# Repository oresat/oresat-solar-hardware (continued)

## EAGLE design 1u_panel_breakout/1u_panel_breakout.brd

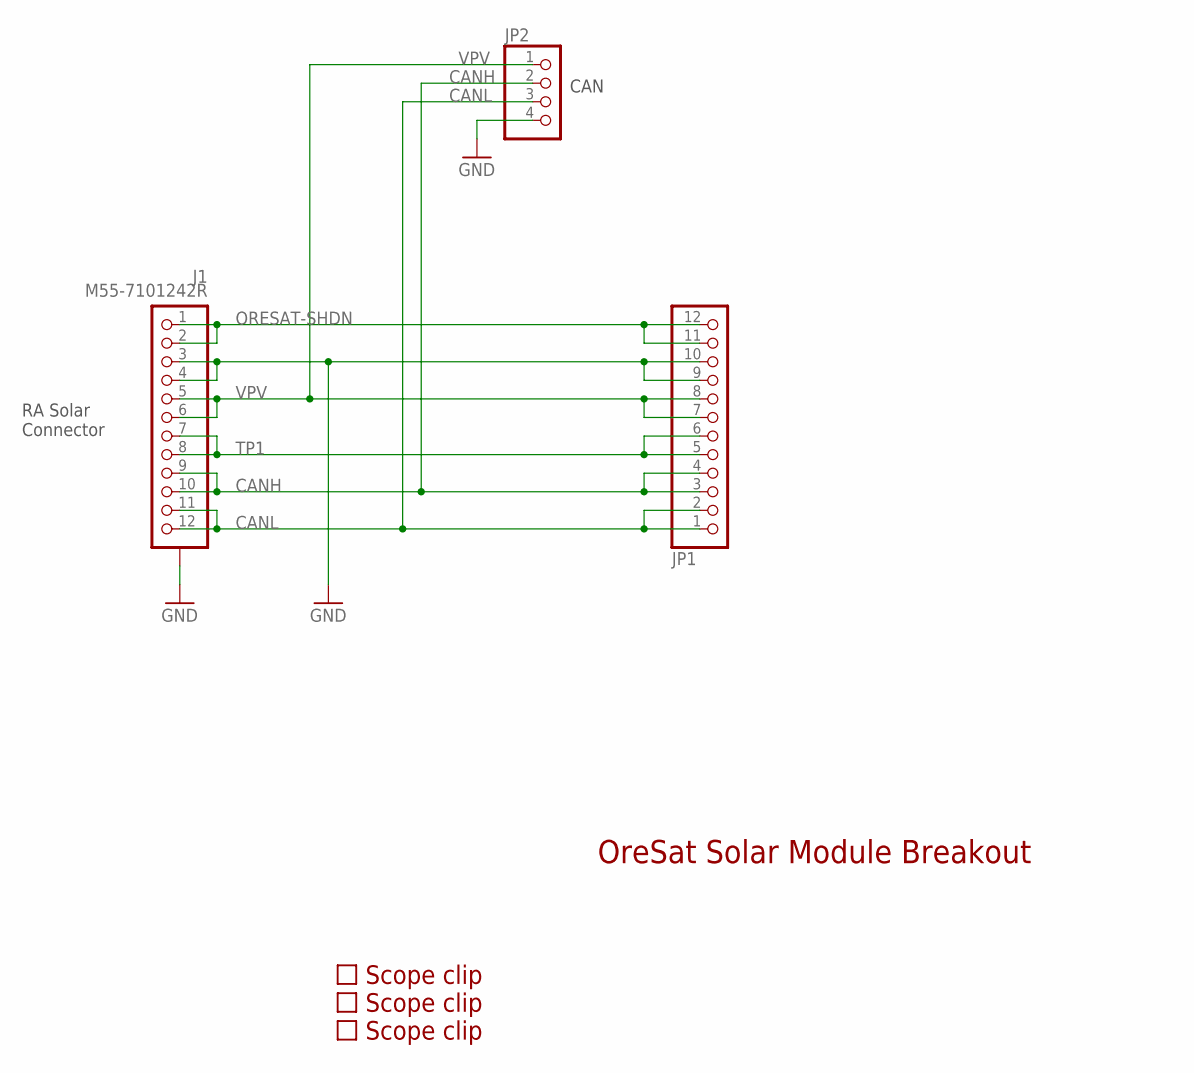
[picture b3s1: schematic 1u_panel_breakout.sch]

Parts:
J1: M55-7101242R
JP1: PINHD-1X12; 1X12
JP2: PINHD-1X4; 1X04
U$1, U$2, U$3: SCOPE_CLIP

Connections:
CANH: J1.9, J1.10, JP1.3, JP1.4, JP2.2
CANL: J1.11, J1.12, JP1.1, JP1.2, JP2.3
GND: J1.3, J1.4, J1.P$1 (SHIELD), J1.P$2 (SHIELD), J1.P$3 (SHIELD), J1.P$4 (SHIELD), JP1.9, JP1.10, JP2.4
ORESAT-SHDN: J1.1, J1.2, JP1.11, JP1.12
TP1: J1.7, J1.8, JP1.5, JP1.6
VPV: J1.5, J1.6, JP1.7, JP1.8, JP2.1

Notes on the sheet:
OreSat Solar Module Breakout
RA Solar Connector
CAN

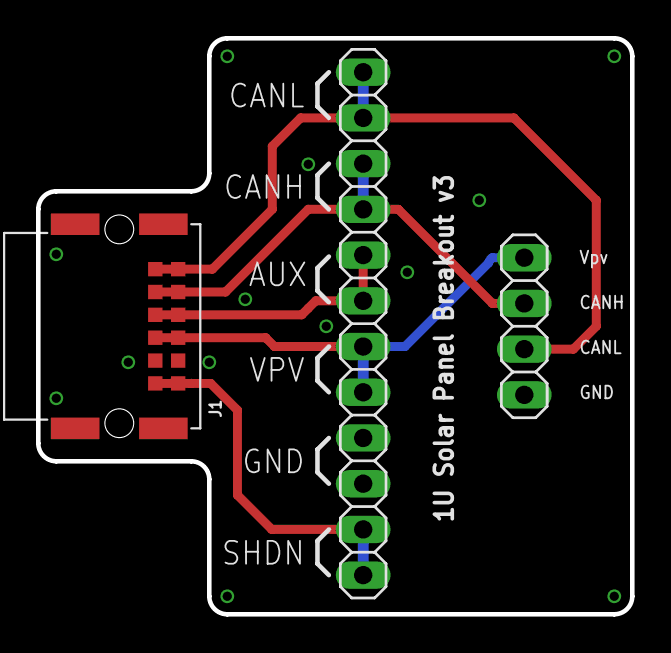
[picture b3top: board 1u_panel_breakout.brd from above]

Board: 2 copper layers, 33.0 x 32.0 mm, 6 parts (0 on the bottom side), 6 nets.

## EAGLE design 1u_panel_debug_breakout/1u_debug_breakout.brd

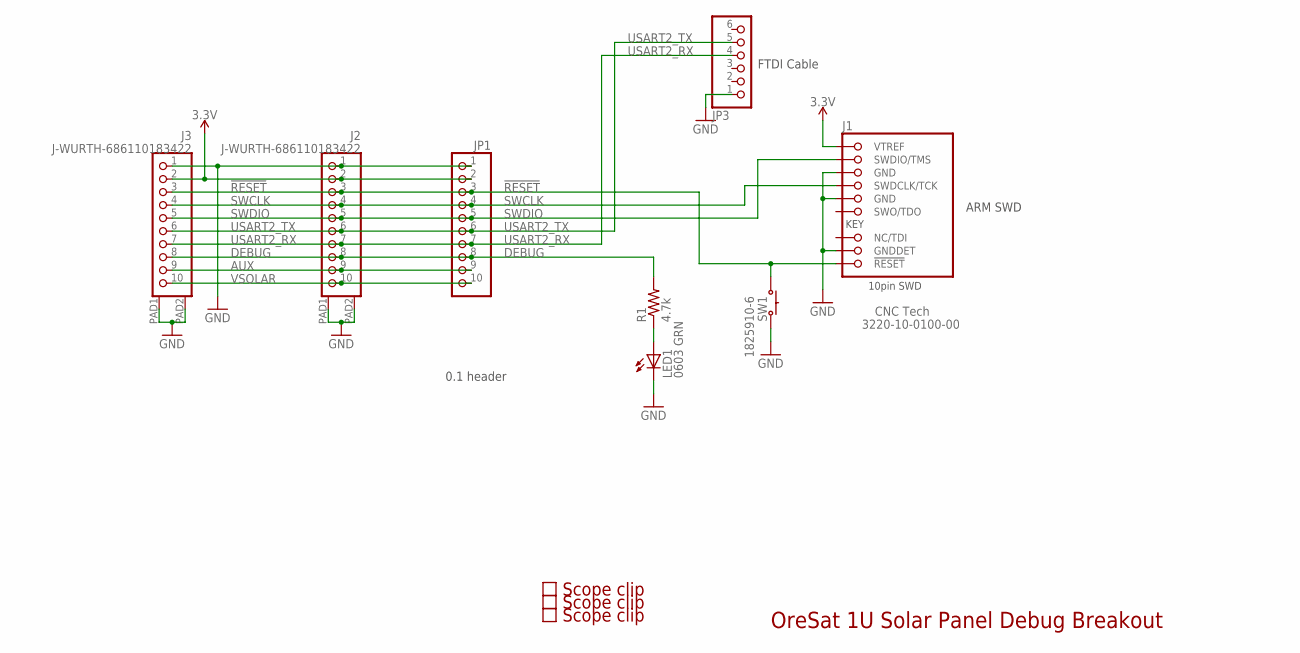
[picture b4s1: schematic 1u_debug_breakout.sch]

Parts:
J1: 1.27MM-SWD-CONNECTOR; 1.27MM_2X5; MPN 3220-10-0100-00
J2, J3: J-WURTH-686110183422
JP1: PINHD-1X10; 1X10
JP3: PINHD-1X6; 1X06
LED1: 0603 GRN; CHIPLED_0603
R1: 4.7k; R0603
SW1: 1825910-6; SWITCH_FSM4JAH
U$1, U$2, U$3: SCOPE_CLIP

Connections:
3.3V: J1.VTREF, J2.2, J3.2, JP1.2
!RESET: J1.!RESET, J2.3, J3.3, JP1.3, SW1.1, SW1.2 (1)
AUX: J2.9, J3.9, JP1.9
DEBUG: J2.8, J3.8, JP1.8, R1.2
GND: J1.GND, J1.GND@2 (GND), J1.GNDDET, J2.1, J2.PAD1, J2.PAD2, J3.1, J3.PAD1, J3.PAD2, JP1.1, JP3.1, LED1.C, SW1.3 (2), SW1.4 (2)
unnamed: LED1.A, R1.1
SWCLK: J1.SWDCLK (SWDCLK/TCK), J2.4, J3.4, JP1.4
SWDIO: J1.SWDIO (SWDIO/TMS), J2.5, J3.5, JP1.5
USART2_RX: J2.7, J3.7, JP1.7, JP3.4
USART2_TX: J2.6, J3.6, JP1.6, JP3.5
VSOLAR: J2.10, J3.10, JP1.10

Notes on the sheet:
OreSat 1U Solar Panel Debug Breakout
0.1 header
FTDI Cable
ARM SWD

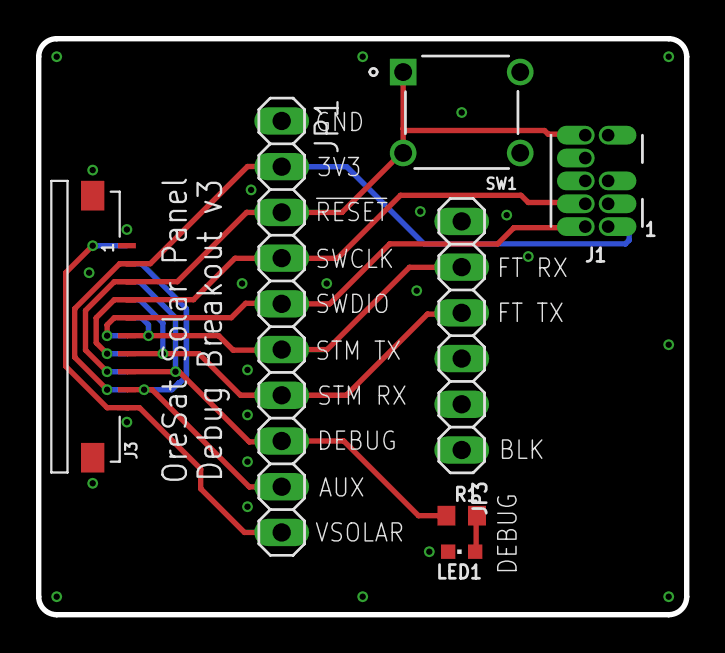
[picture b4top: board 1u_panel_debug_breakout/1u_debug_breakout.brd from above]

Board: 2 copper layers, 36.0 x 32.0 mm, 11 parts (1 on the bottom side), 11 nets.

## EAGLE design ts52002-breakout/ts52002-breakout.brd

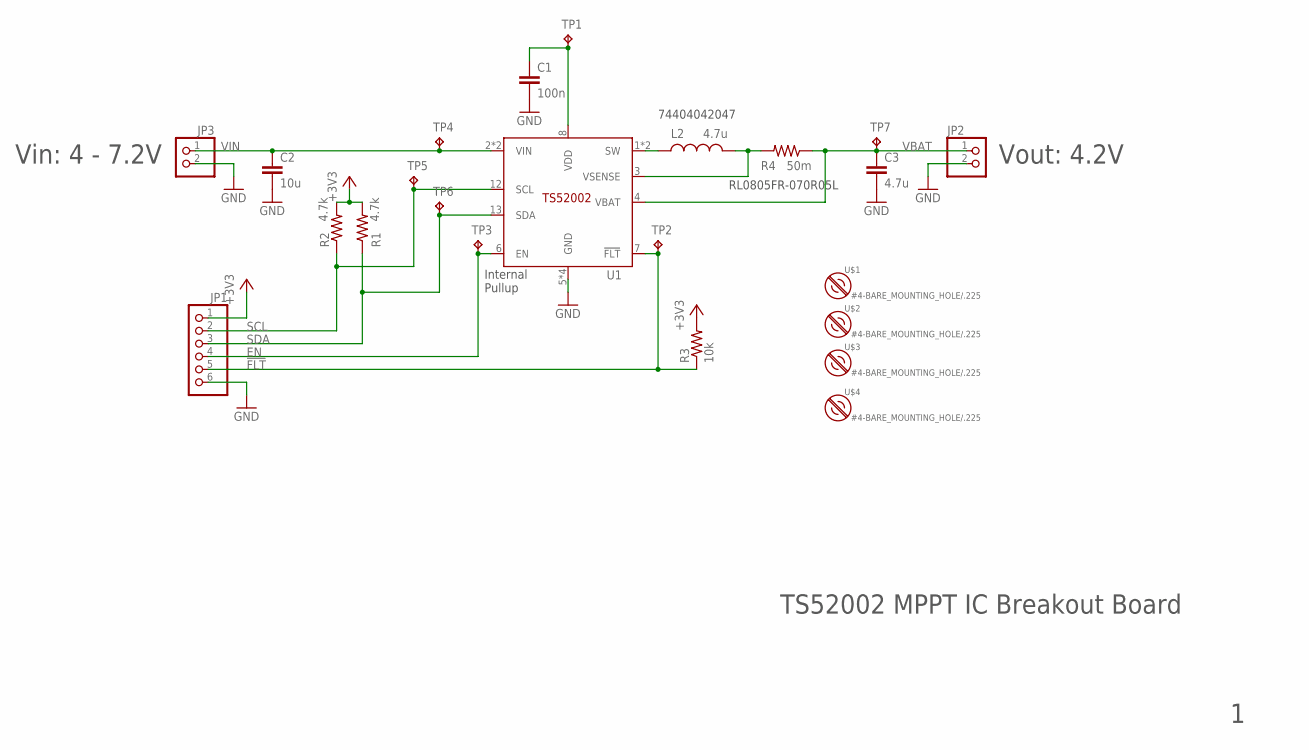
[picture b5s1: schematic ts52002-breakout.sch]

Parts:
C1: 100n; .0603-B-NOSILK
C2: 10u; .0805-B-NOSILK
C3: 4.7u; .0805-B-NOSILK
JP1: PINHD-1X6; 1X06
JP2, JP3: PINHD-1X2; 1X02
L2: 4.7u; WURTH-4518
R1, R2: 4.7k; .0603-B-NOSILK
R3: 10k; .0603-B-NOSILK
R4: 50m; .0805-B-NOSILK
TP1, TP2, TP3, TP4, TP5, TP6, TP7: TPPAD1-13; P1-13
U1: TS52002; QFN-32-WITH-CENTER-PAD
U$1, U$2, U$3, U$4: #4-BARE_MOUNTING_HOLE/.225; #4/.225-BARE+HEAD_OR_SMALL_NUT

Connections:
!FLT: JP1.5, R3.1, TP2.TP, U1.7 (!FLT)
+3V3: JP1.1, R1.2, R2.2, R3.2
EN: JP1.4, TP3.TP, U1.6 (EN)
GND: C1.2, C2.2, C3.2, JP1.6, JP2.2, JP3.2, U1.5 (GND), U1.15 (GND), U1.16 (GND), U1.PAD (GND)
SCL: JP1.2, R2.1, TP5.TP, U1.12 (SCL)
SDA: JP1.3, R1.1, TP6.TP, U1.13 (SDA)
SW: L2.P$1 (1), U1.1 (SW), U1.14 (SW)
VBAT: C3.1, JP2.1, R4.1, TP7.TP, U1.4 (VBAT)
VDD: C1.1, TP1.TP, U1.8 (VDD)
VIN: C2.1, JP3.1, TP4.TP, U1.2 (VIN), U1.11 (VIN)
VSENSE: L2.P$2 (2), R4.2, U1.3 (VSENSE)

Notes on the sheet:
74404042047
RL0805FR-070R05L
TS52002 MPPT IC Breakout Board
Vin: 4 - 7.2V
Vout: 4.2V
Internal Pullup

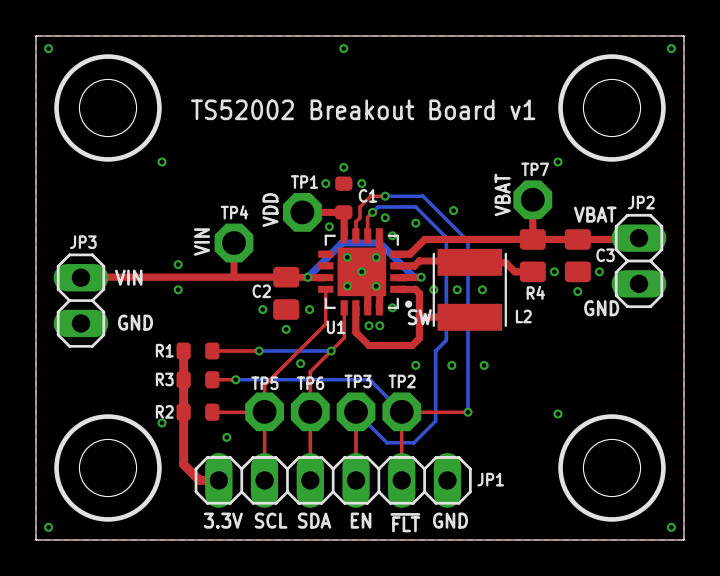
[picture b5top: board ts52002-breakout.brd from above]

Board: 2 copper layers, 36.0 x 28.0 mm, 23 parts (0 on the bottom side), 11 nets.

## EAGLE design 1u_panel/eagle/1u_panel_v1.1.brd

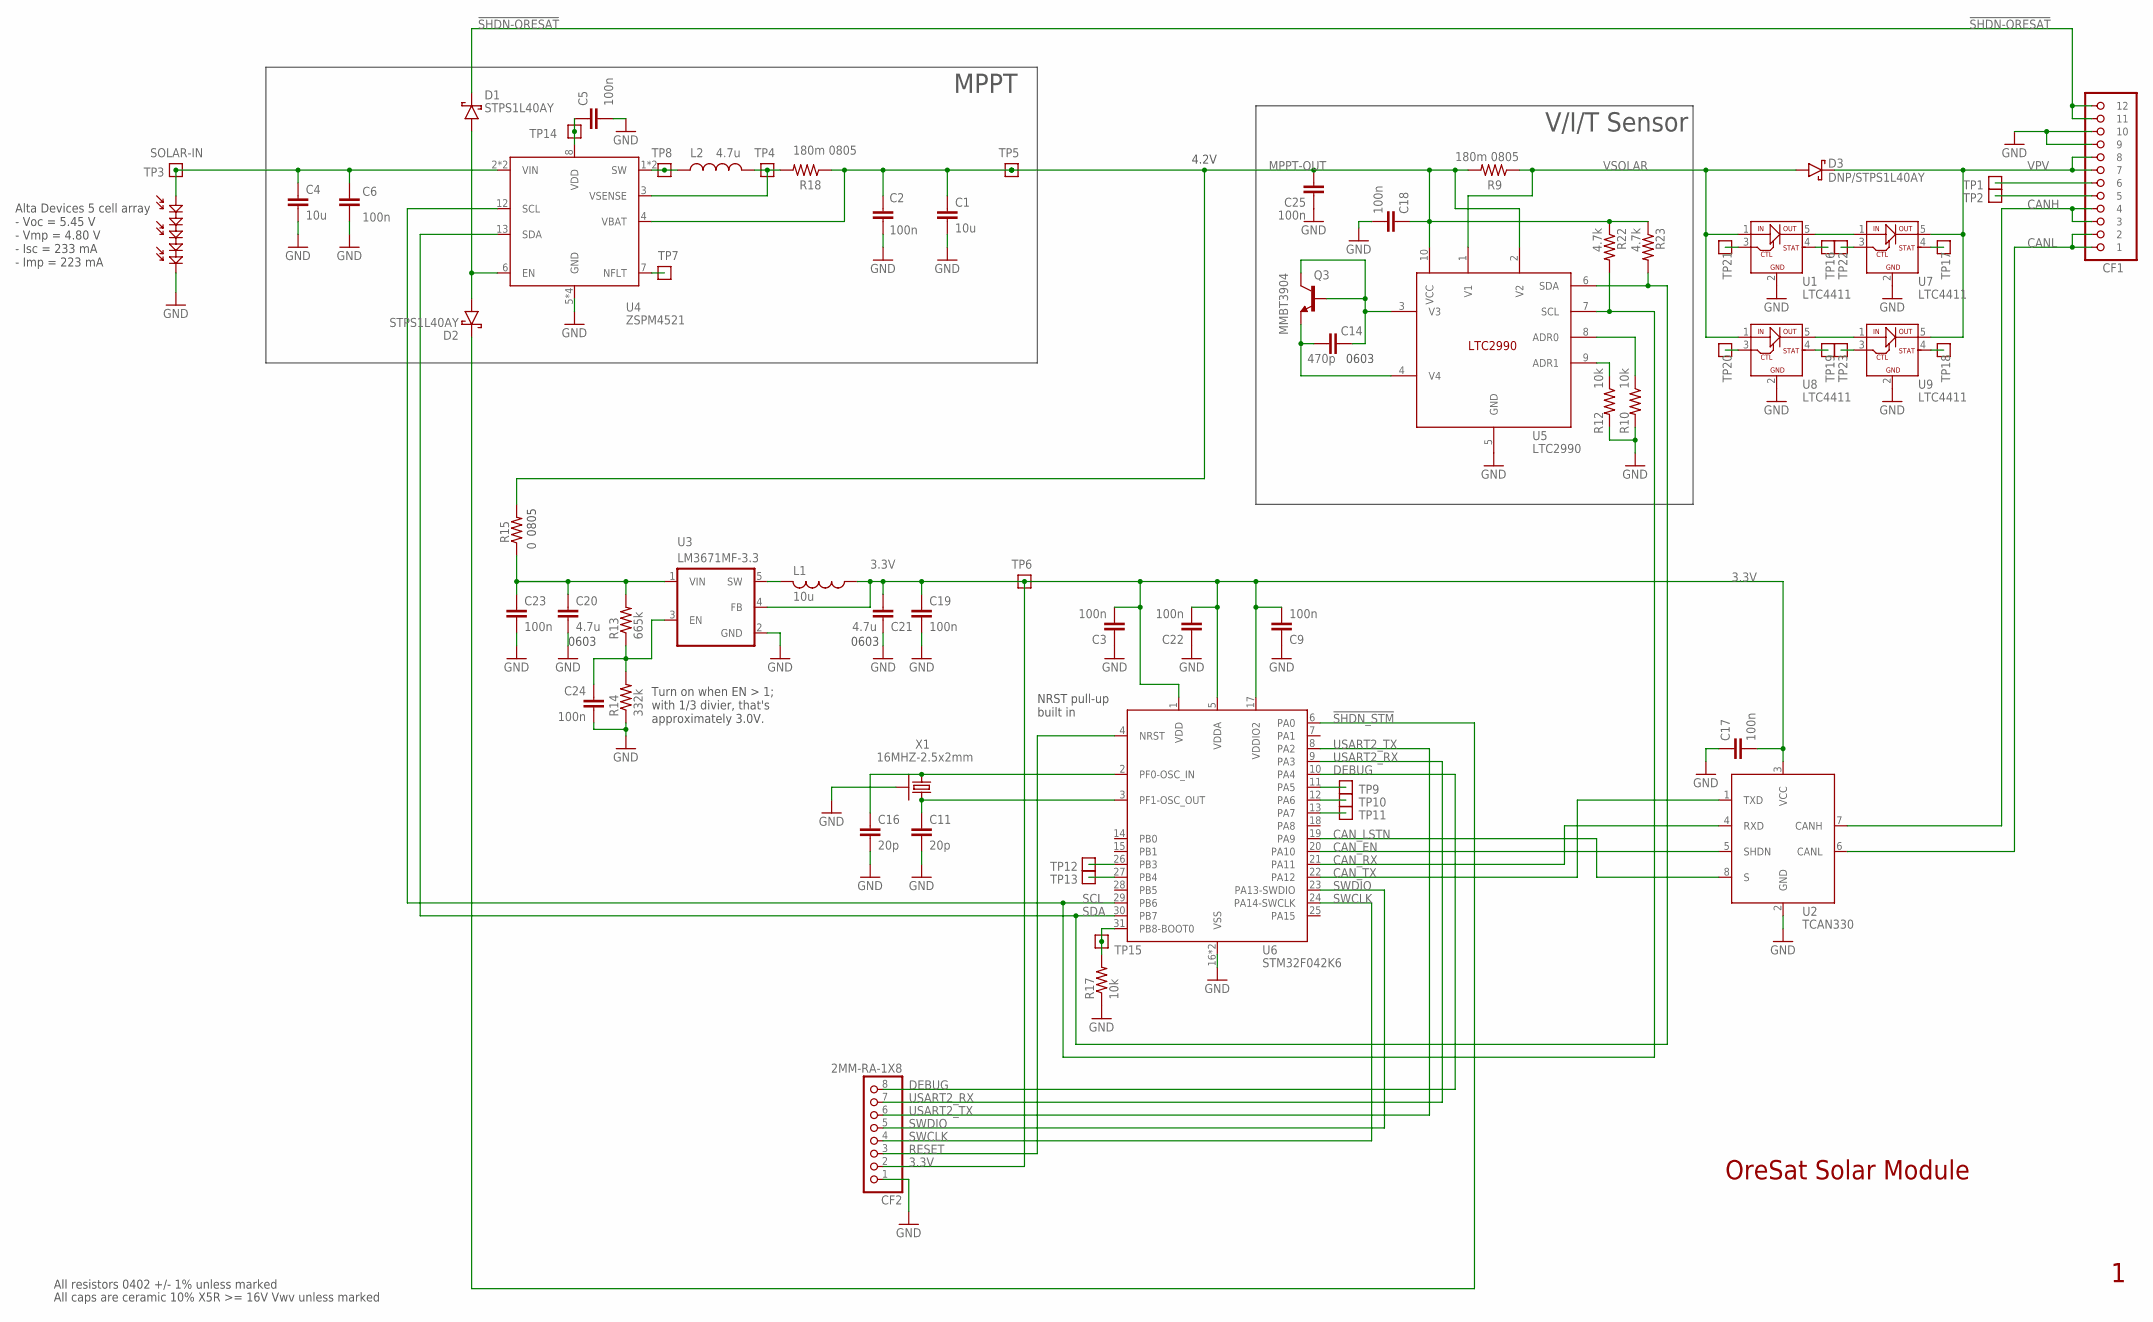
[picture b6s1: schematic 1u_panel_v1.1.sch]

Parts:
C1, C4: 10u; 1206-B; MPN GRM31CR71A226KE15L
C2, C3, C5, C6, C9, C17, C18, C19, C22, C23, C24, C25: 100n; .0402-B-NOSILK; MPN CL05B104KO5NNNC
C11, C16: 20p; .0402-B-NOSILK; MPN CL05C200JB51PNC
C14: 470p; .0603-B-NOSILK; MPN CL10A226MP8NUNE
C20, C21: 4.7u; C0603; MPN CL05B104KO5NNNC
CF1: 15220122401000; CON-1.27-F-HARTING-1522012X601XXX; MPN 15220122401000
CF2: 2MM-RA-1X8; CF-2MM-RA-1X8-PRECIDIP-831; MPN 831-87-050-40-001101
D1, D2: STPS1L40AY; DO214AC; MPN STPS1L40AY
D3: DNP/STPS1L40AY; DO214AC; MPN STPS1L40AY
L1: 10u; L2012C; MPN CB2012T100KR
L2: 4.7u; VISHAY-DALE-IFSR-1515AHER; MPN IFSC1515AHER220M01
PV1: ALTA-5-CELL-ARRAYALTA-FIVE-CELL-SLOT; ALTA-FIVE-CELL-THROUGH-SLOT
Q3: MMBT3904; SOT23HOLE; MPN MMBT3904
R9, R18: 180m 0805; .0805-B-NOSILK; MPN RCWE0805R180FKEA
R10, R12: 10k; .0402-B-NOSILK; MPN MCR01MZPF1002
R13: 665k; .0402-B-NOSILK; MPN RC1005F6653CS
R14: 332k; .0402-B-NOSILK; MPN RC1005F3323CS
R15: 0; .0805-B-NOSILK; MPN MCR10EZPJ000
R17: 10k; .0402-B-NOSILK; MPN RC1005F6653CS
R22, R23: 4.7k; .0402-B-NOSILK; MPN TRR01MZPF4701
TP1, TP2, TP3, TP4, TP5, TP6, TP7, TP8, TP9, TP10, TP11, TP12, TP13, TP14, TP15, TP16, TP17, TP18, TP19, TP20, TP21, TP22, TP23: TEST-POINT; 2MM-TEST-POINT
U1, U7, U8, U9: LTC4411; SOT23-5-B
U2: TCAN330; SOT23-8_TI-DCN; MPN TCAN330GDCNT
U3: LM3671MF-3.3; SOT23-5; MPN LM3671MF-3.3/NOPB
U4: ZSPM4521; QFN-16(4X4)
U5: LTC2990; MSOP10; MPN LTC2990CMS#PBF
U6: STM32F042K6; QFP32-7X7; MPN STM32F042K6T7
X1: 16MHZ-2.5x2mm; CRYSTAL_2.5X2; MPN ECS-160-10-36Q-ES-TR

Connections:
3.3V: C3.2, C9.2, C17.2, C19.1, C21.1, C22.2, CF2.2, L1.1, TP6.1, U2.3 (VCC), U3.4 (FB), U6.1 (VDD), U6.5 (VDDA), U6.17 (VDDIO2)
!SHDN-ORESAT: CF1.11, CF1.12, D1.C
!SHDN_STM: D2.C, U6.6 (PA0)
ADDRSELECT: R10.1, U5.8 (ADR0)
ADR1: R12.1, U5.9 (ADR1)
BOOT: R17.2, TP15.1, U6.31 (PB8-BOOT0)
CANH: CF1.3, CF1.4, U2.7 (CANH)
CANL: CF1.1, CF1.2, U2.6 (CANL)
CAN_EN: U2.5 (SHDN), U6.20 (PA10)
CAN_LSTN: U2.8 (S), U6.19 (PA9)
CAN_RX: U2.4 (RXD), U6.21 (PA11)
CAN_TX: U2.1 (TXD), U6.22 (PA12)
CRYSTALIN: C16.1, U6.2 (PF0-OSC_IN), X1.1
CRYSTALOUT: C11.1, U6.3 (PF1-OSC_OUT), X1.3 (2)
DEBUG: CF2.8, U6.10 (PA4)
GND: C1.2, C2.2, C3.1, C4.2, C5.2, C6.2, C9.1, C11.2, C16.2, C17.1, C18.2, C19.2, C20.2, C21.2, C22.1, C23.2, C24.2, C25.1, CF1.9, CF1.10, CF2.1, PV1.NEG1 (NEG), PV1.NEG2 (NEG), R10.2, R12.2, R14.1, R17.1, U1.2 (GND), U2.2 (GND), U3.2 (GND), U4.5 (GND), U4.15 (GND), U4.16 (GND), U4.PAD (GND), U5.5 (GND), U6.16 (VSS), U6.32 (VSS), U7.2 (GND), U8.2 (GND), U9.2 (GND), X1.2 (SHIELD), X1.4 (SHIELD)
MPPT-OUT: C1.1, C2.1, C18.1, C25.2, R9.2, R15.2, R18.1, R22.1, R23.1, TP5.1, U4.4 (VBAT), U5.2 (V2), U5.10 (VCC)
unnamed: C20.1, C23.1, R13.2, R15.1, U3.1 (VIN)
unnamed: L2.2, TP8.1, U4.1 (SW), U4.14 (SW)
unnamed: CF1.6, TP1.1
unnamed: CF1.5, TP2.1
unnamed: L2.1, R18.2, TP4.1, U4.3 (VSENSE)
unnamed: TP9.1, U6.11 (PA5)
unnamed: TP10.1, U6.12 (PA6)
unnamed: TP11.1, U6.13 (PA7)
unnamed: TP12.1, U6.26 (PB3)
unnamed: TP13.1, U6.27 (PB4)
unnamed: C5.1, TP14.1, U4.8 (VDD)
unnamed: U1.5 (OUT), U7.1 (IN)
unnamed: TP7.1, U4.7 (NFLT)
unnamed: U8.5 (OUT), U9.1 (IN)
unnamed: TP16.1, U1.4 (STAT)
unnamed: TP23.1, U9.3 (CTL)
unnamed: TP17.1, U7.4 (STAT)
unnamed: TP18.1, U9.4 (STAT)
unnamed: TP19.1, U8.4 (STAT)
unnamed: TP22.1, U7.3 (CTL)
unnamed: TP21.1, U1.3 (CTL)
unnamed: TP20.1, U8.3 (CTL)
RESET: CF2.3, U6.4 (NRST)
SCL: R22.2, U4.12 (SCL), U5.7 (SCL), U6.29 (PB6)
SDA: R23.2, U4.13 (SDA), U5.6 (SDA), U6.30 (PB7)
SOLAR-IN: C4.1, C6.1, PV1.POS1 (POS), PV1.POS2 (POS), TP3.1, U4.2 (VIN), U4.11 (VIN)
STEPD: L1.2, U3.5 (SW)
SWCLK: CF2.4, U6.24 (PA14-SWCLK)
SWDIO: CF2.5, U6.23 (PA13-SWDIO)
USART2_RX: CF2.7, U6.9 (PA3)
USART2_TX: CF2.6, U6.8 (PA2)
V3: C14.2, Q3.1 (B), Q3.3 (C), U5.3 (V3)
V4: C14.1, Q3.2 (E), U5.4 (V4)
VDIV: C24.1, R13.1, R14.2, U3.3 (EN)
VPV: CF1.7, CF1.8, D3.C, U7.5 (OUT), U9.5 (OUT)
VSOLAR: D3.A, R9.1, U1.1 (IN), U5.1 (V1), U8.1 (IN)
ZSPM_EN: D1.A, D2.A, U4.6 (EN)

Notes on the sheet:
Alta Devices 5 cell array - Voc = 5.45 V - Vmp = 4.80 V - Isc = 233 mA - Imp = 223 mA
NRST pull-up built in
Turn on when EN > 1; with 1/3 divier, that's approximately 3.0V.
OreSat Solar Module
V/I/T Sensor
MPPT
All resistors 0402 +/- 1% unless marked
All caps are ceramic 10% X5R >= 16V Vwv unless marked
4.2V
0603
0805

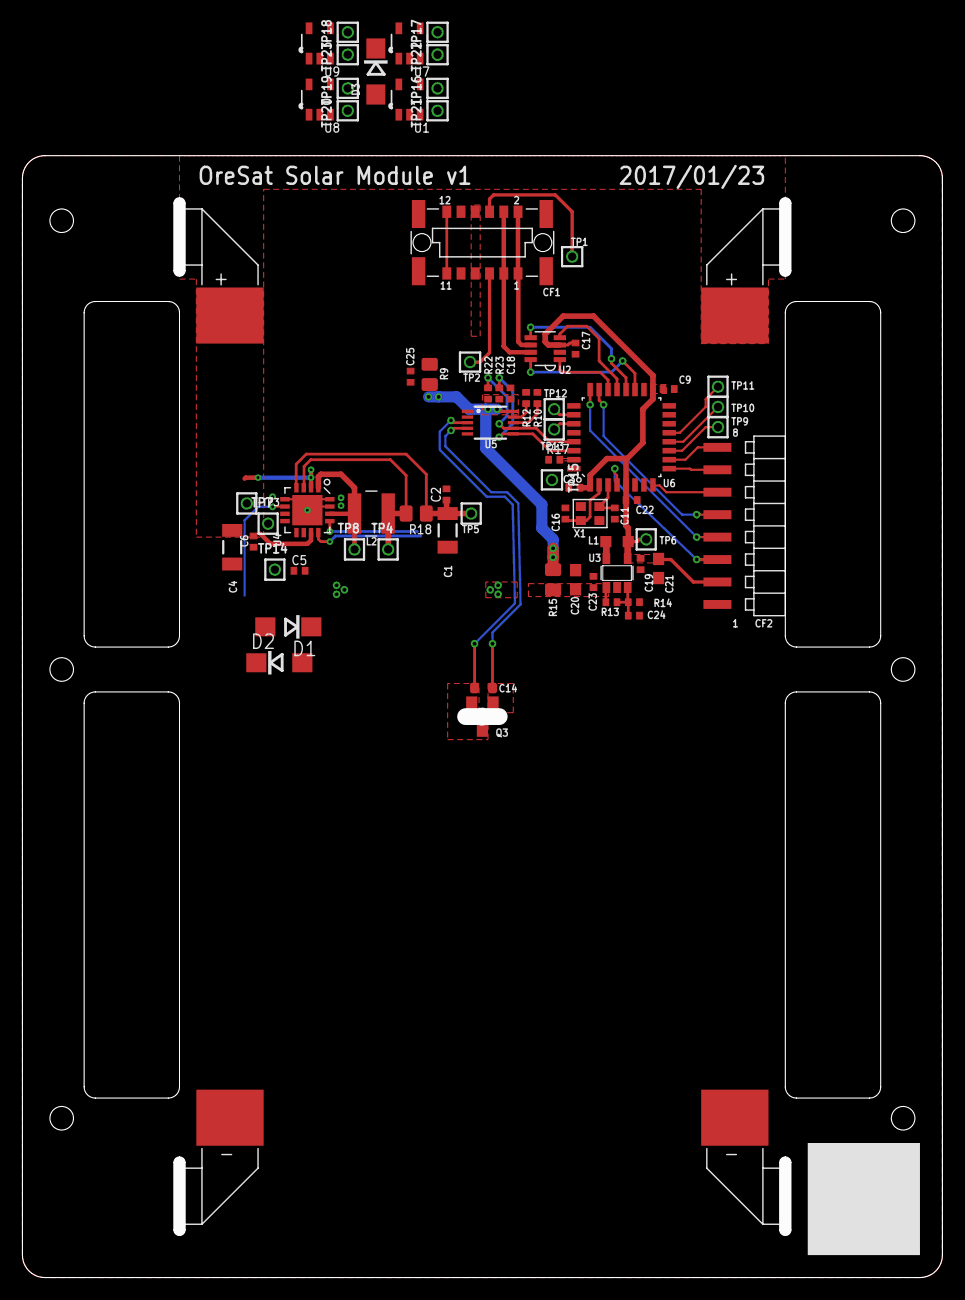
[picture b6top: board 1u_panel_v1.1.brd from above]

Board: 2 copper layers, 82.0 x 100.0 mm, 71 parts (1 on the bottom side), 54 nets.

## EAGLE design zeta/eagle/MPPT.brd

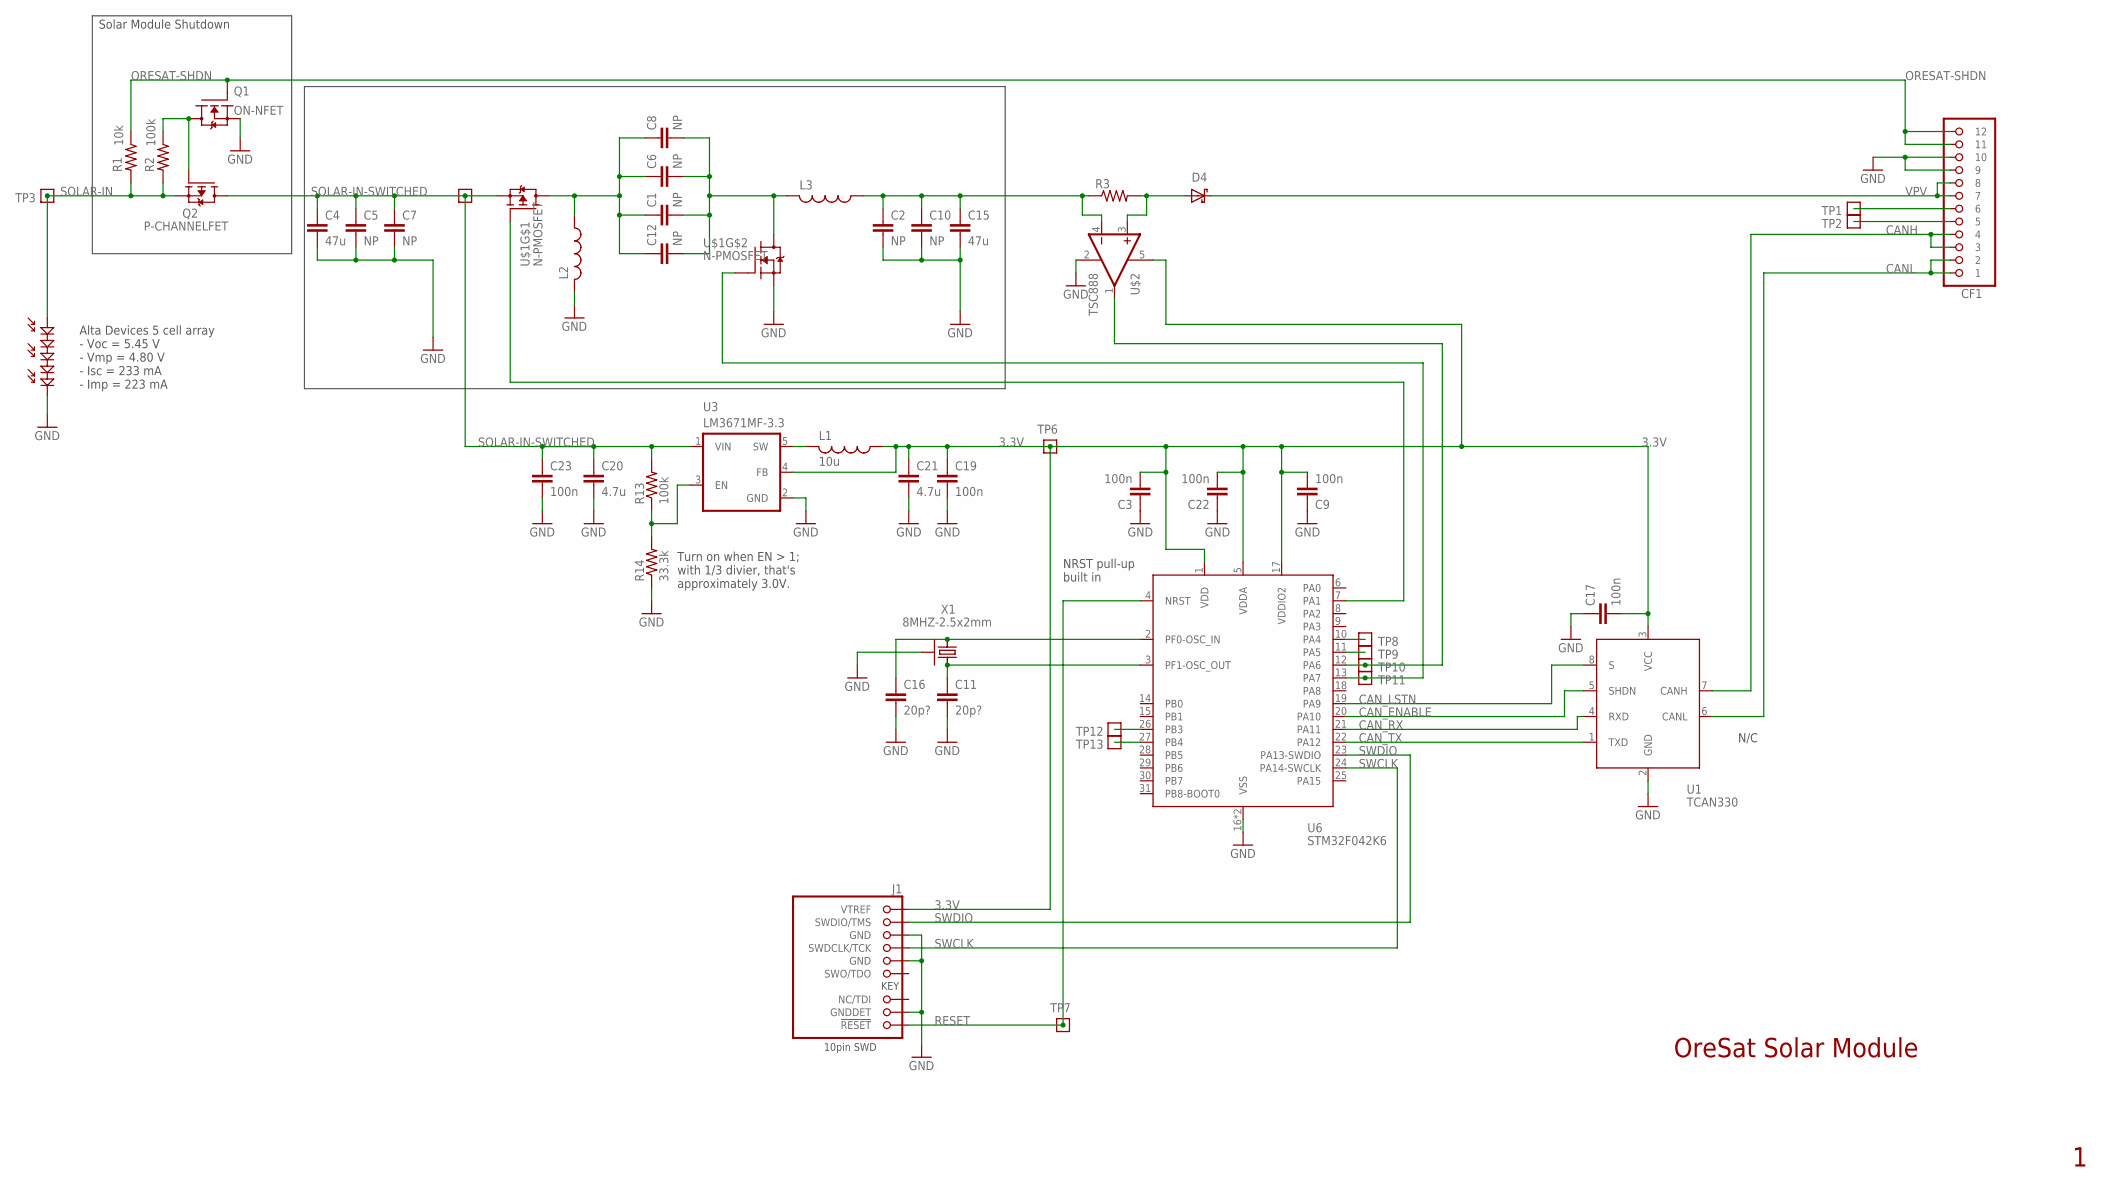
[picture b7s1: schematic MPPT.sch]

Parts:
C1, C2, C5, C6, C7, C8, C10, C12: NP; C0603
C3, C9, C17, C19, C22, C23: 100n; .0402-B-NOSILK
C4, C15: 47u; C0603
C11, C16: 20p?; .0402-B-NOSILK
C20, C21: 4.7u; C0603
CF1: ORESAT-SOLARPANEL-12PIN; CON-1.27-F-HARTING-1522012X601XXX
D2: ALTA-5-CELL-ARRAY; ALTA-FIVE-CELL
D4: SOD123-B SCHOTTKY; SOD123-B
J1: 1.27MM-SWD-CONNECTOR; 1.27MM_2X5
L1: 10u; L2012C
L2, L3: L-USL1812; L1812
Q1: ON-NFET; SOT23
Q2: P-CHANNELFET; SO8
R1: 10k; .0402-B-NOSILK
R2, R13: 100k; .0402-B-NOSILK
R3: R-US_R0603; R0603
R14: 33.3k; .0402-B-NOSILK
TP1, TP2, TP3, TP4, TP6, TP7, TP8, TP9, TP10, TP11, TP12, TP13: TEST-POINT; 2MM-TEST-POINT
U1: TCAN330; SOT23-8_TI-DCN
U3: LM3671MF-3.3; SOT23-5
U6: STM32F042K6; QFP32-7X7
U$1: N-PMOSFET; 5X6POWERFLAT
U$2: TSC888; SOT23-5
X1: 8MHZ-2.5x2mm; CRYSTAL_2.5X2

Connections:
3.3V: C3.2, C9.2, C17.2, C19.1, C21.1, C22.2, J1.VTREF, L1.1, TP6.1, U1.3 (VCC), U3.4 (FB), U6.1 (VDD), U6.5 (VDDA), U6.17 (VDDIO2), U$2.5 (V+)
CANH: CF1.3, CF1.4, U1.7 (CANH)
CANL: CF1.1, CF1.2, U1.6 (CANL)
CAN_ENABLE: U1.5 (SHDN), U6.20 (PA10)
CAN_LSTN: U1.8 (S), U6.19 (PA9)
CAN_RX: U1.4 (RXD), U6.21 (PA11)
CAN_TX: U1.1 (TXD), U6.22 (PA12)
CRYSTALIN: C16.1, U6.2 (PF0-OSC_IN), X1.1
CRYSTALOUT: C11.1, U6.3 (PF1-OSC_OUT), X1.3 (2)
GND: C2.2, C3.1, C4.2, C5.2, C7.2, C9.1, C10.2, C11.2, C15.2, C16.2, C17.1, C19.2, C20.2, C21.2, C22.1, C23.2, CF1.9, CF1.10, D2.NEG, J1.GND, J1.GND@2 (GND), J1.GNDDET, L2.2, Q1.2 (S), R14.1, U1.2 (GND), U3.2 (GND), U6.16 (VSS), U6.32 (VSS), U$1.S2 (S), U$2.2 (GND), X1.2 (SHIELD), X1.4 (SHIELD)
N6: Q1.3 (D), Q2.4 (G), R2.1
unnamed: C1.1, C6.1, C8.1, C12.1, L2.1, U$1.D1 (D), U$1.D11 (D), U$1.D12 (D), U$1.D13 (D), U$1.D14 (D)
unnamed: C1.2, C6.2, C8.2, C12.2, L3.2, U$1.D2 (D), U$1.D21 (D), U$1.D22 (D), U$1.D23 (D), U$1.D24 (D)
unnamed: CF1.6, TP1.1
unnamed: CF1.5, TP2.1
unnamed: TP8.1, U6.10 (PA4)
unnamed: TP9.1, U6.11 (PA5)
unnamed: TP10.1, U6.12 (PA6), U$2.1 (OUT)
unnamed: TP11.1, U6.13 (PA7), U$1.G2 (G)
unnamed: TP12.1, U6.26 (PB3)
unnamed: TP13.1, U6.27 (PB4)
unnamed: C2.1, C10.1, C15.1, L3.1, R3.1, U$2.4 (-IN)
unnamed: U6.7 (PA1), U$1.G1 (G)
unnamed: D4.A (ANODE), R3.2, U$2.3 (+IN)
ORESAT-SHDN: CF1.11, CF1.12, Q1.1 (G), R1.1
RESET: J1.!RESET, TP7.1, U6.4 (NRST)
SOLAR-IN: D2.POS, Q2.1 (S), Q2.2 (S), Q2.3 (S), R1.2, R2.2, TP3.1
SOLAR-IN-SWITCHED: C4.1, C5.1, C7.1, C20.1, C23.1, Q2.5 (D), Q2.6 (D), Q2.7 (D), Q2.8 (D), R13.2, TP4.1, U3.1 (VIN), U$1.S1 (S)
STEPD: L1.2, U3.5 (SW)
SWCLK: J1.SWDCLK (SWDCLK/TCK), U6.24 (PA14-SWCLK)
SWDIO: J1.SWDIO (SWDIO/TMS), U6.23 (PA13-SWDIO)
VDIV: R13.1, R14.2, U3.3 (EN)
VPV: CF1.7, CF1.8, D4.K (CATHODE)

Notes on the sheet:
Alta Devices 5 cell array - Voc = 5.45 V - Vmp = 4.80 V - Isc = 233 mA - Imp = 223 mA
N/C
NRST pull-up built in
Turn on when EN > 1; with 1/3 divier, that's approximately 3.0V.
OreSat Solar Module
Solar Module Shutdown

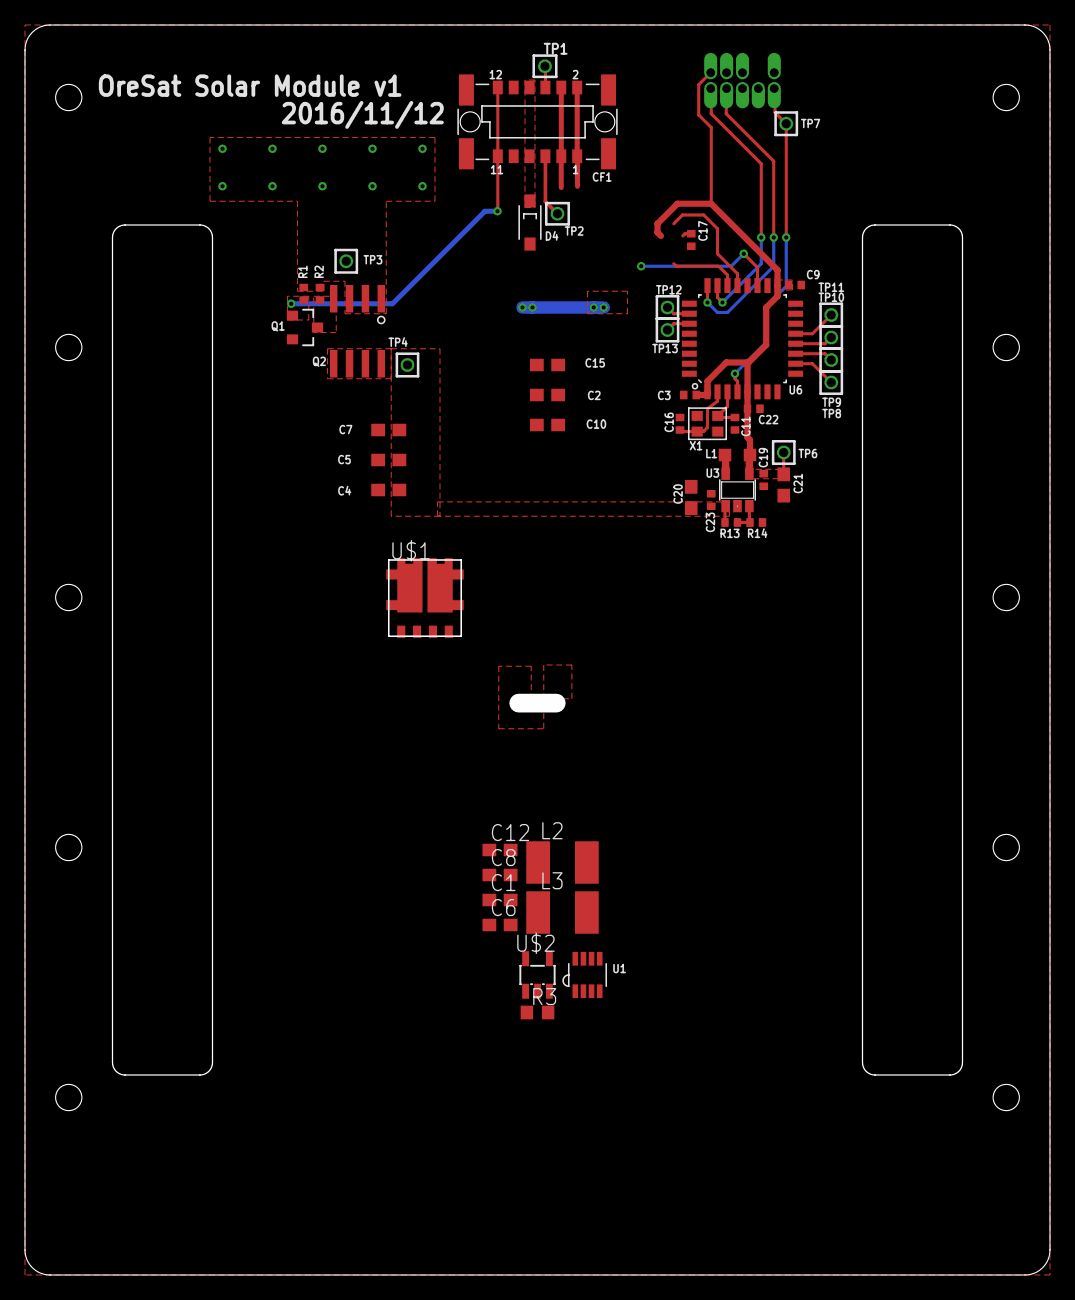
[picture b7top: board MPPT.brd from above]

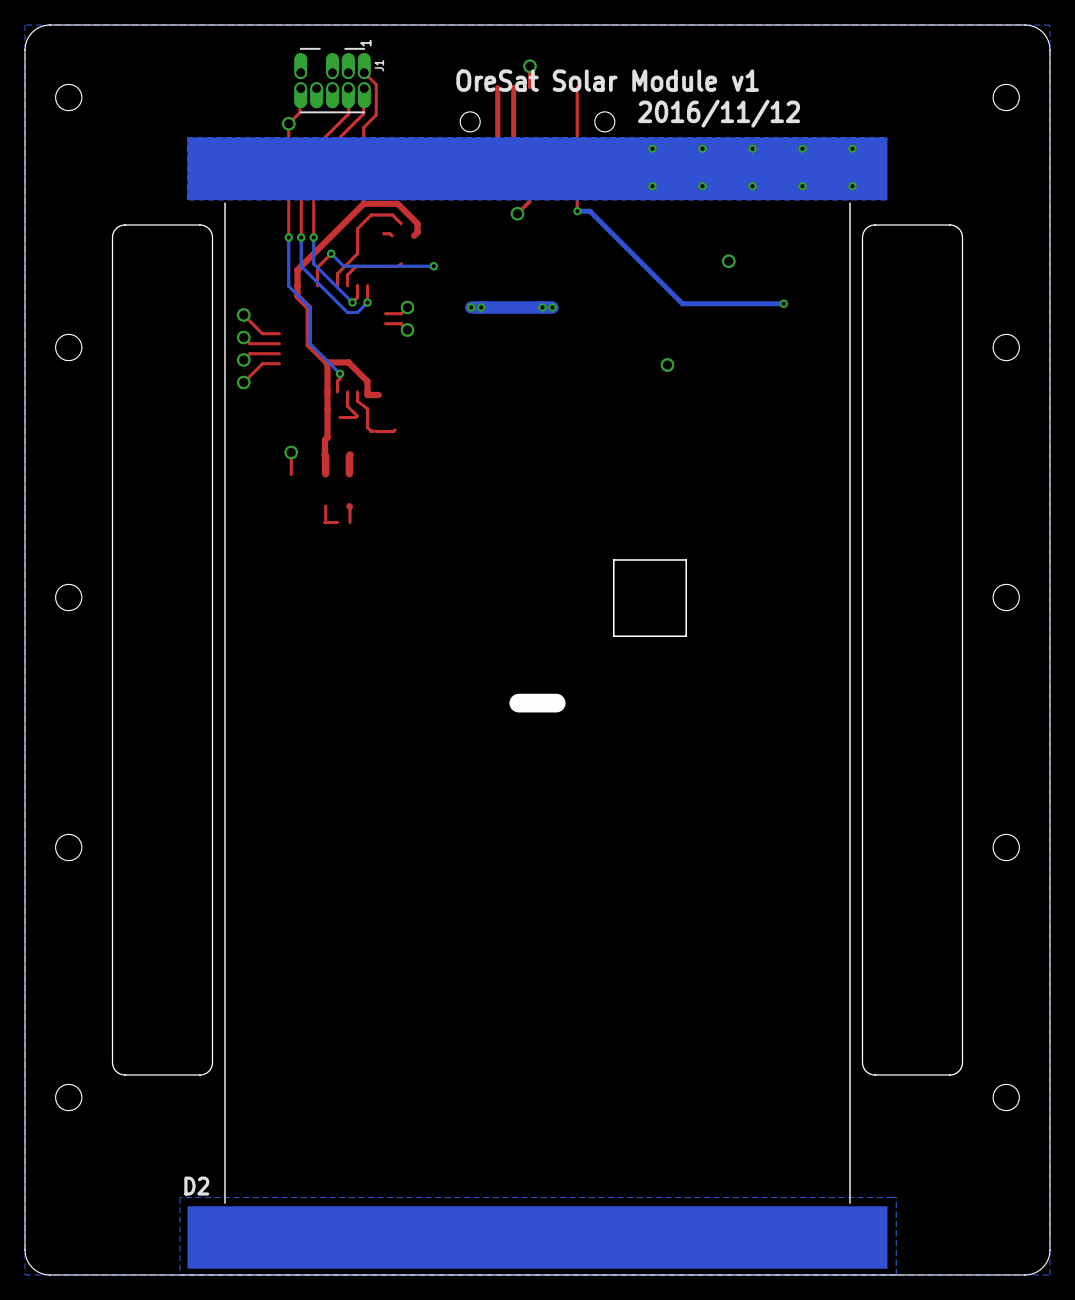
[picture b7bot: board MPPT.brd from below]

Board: 2 copper layers, 82.0 x 100.0 mm, 52 parts (2 on the bottom side), 33 nets.

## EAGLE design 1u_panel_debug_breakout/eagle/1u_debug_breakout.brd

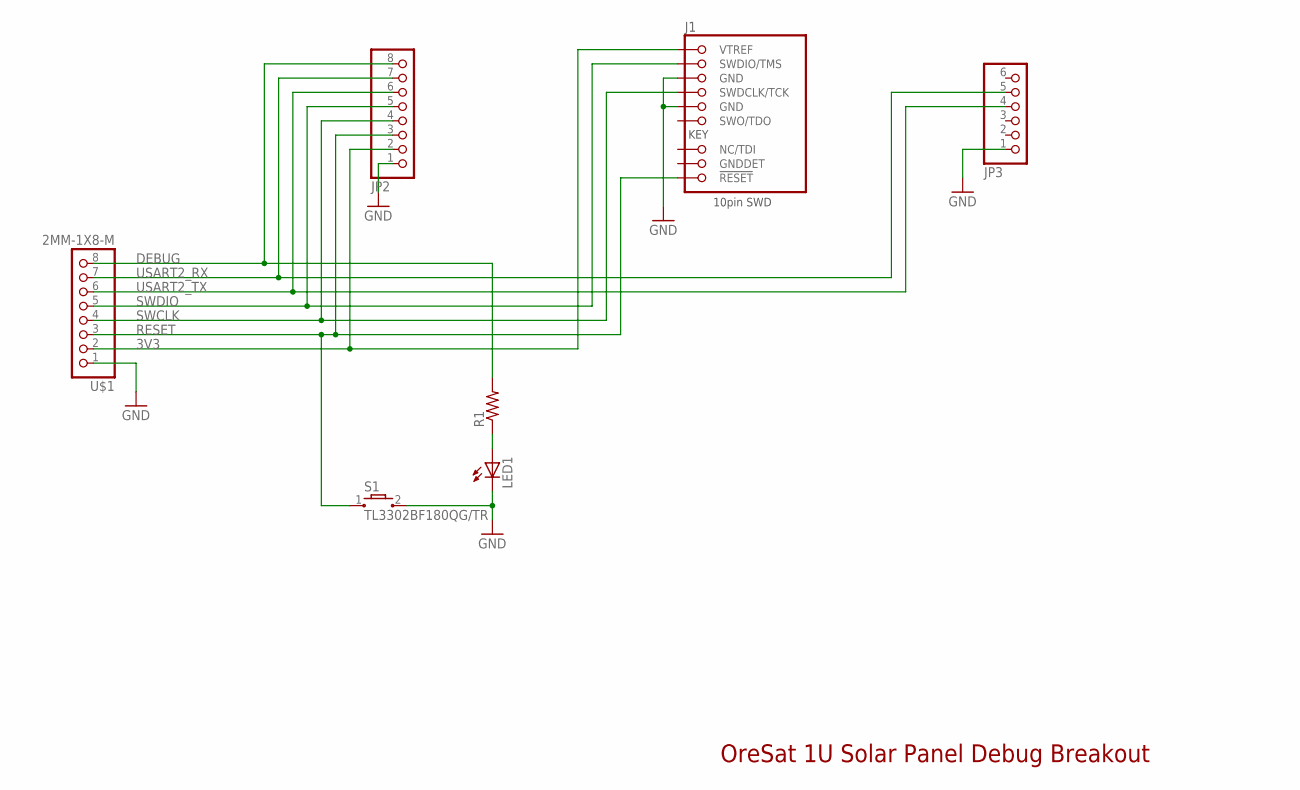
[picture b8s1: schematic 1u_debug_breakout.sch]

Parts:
J1: 1.27MM-SWD-CONNECTOR; 1.27MM_2X5
JP2: PINHD-1X8; 1X08
JP3: PINHD-1X6; 1X06
LED1: LEDCHIPLED_0603; CHIPLED_0603
R1: R-US_R0603; R0603
S1: TL3302BF180QG/TR; TL3302_GULL_WING
U$1: 2MM-1X8-M; CF-2MM-1X8-PRECIDIP-880

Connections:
3V3: J1.VTREF, JP2.2, U$1.2
DEBUG: JP2.8, R1.2, U$1.8
GND: J1.GND, J1.GND@2 (GND), JP2.1, JP3.1, LED1.C, S1.2, U$1.1
unnamed: LED1.A, R1.1
RESET: J1.!RESET, JP2.3, S1.1, U$1.3
SWCLK: J1.SWDCLK (SWDCLK/TCK), JP2.4, U$1.4
SWDIO: J1.SWDIO (SWDIO/TMS), JP2.5, U$1.5
USART2_RX: JP2.7, JP3.5, U$1.7
USART2_TX: JP2.6, JP3.4, U$1.6

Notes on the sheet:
OreSat 1U Solar Panel Debug Breakout

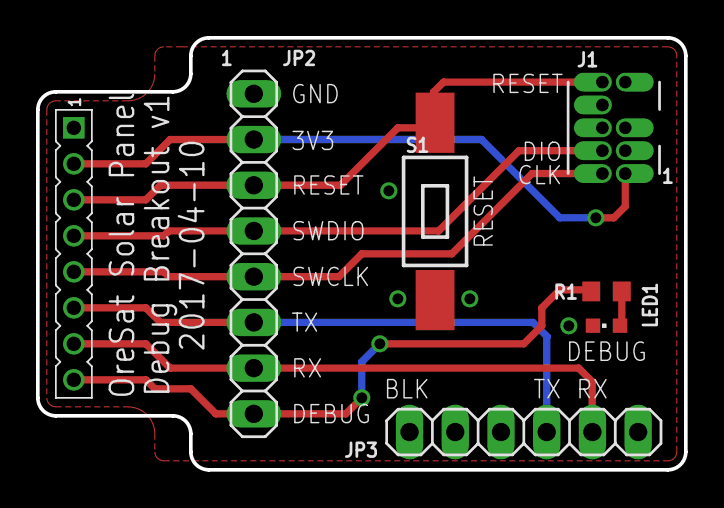
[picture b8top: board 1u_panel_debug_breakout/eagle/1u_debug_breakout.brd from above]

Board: 2 copper layers, 36.0 x 24.0 mm, 7 parts (0 on the bottom side), 9 nets.
